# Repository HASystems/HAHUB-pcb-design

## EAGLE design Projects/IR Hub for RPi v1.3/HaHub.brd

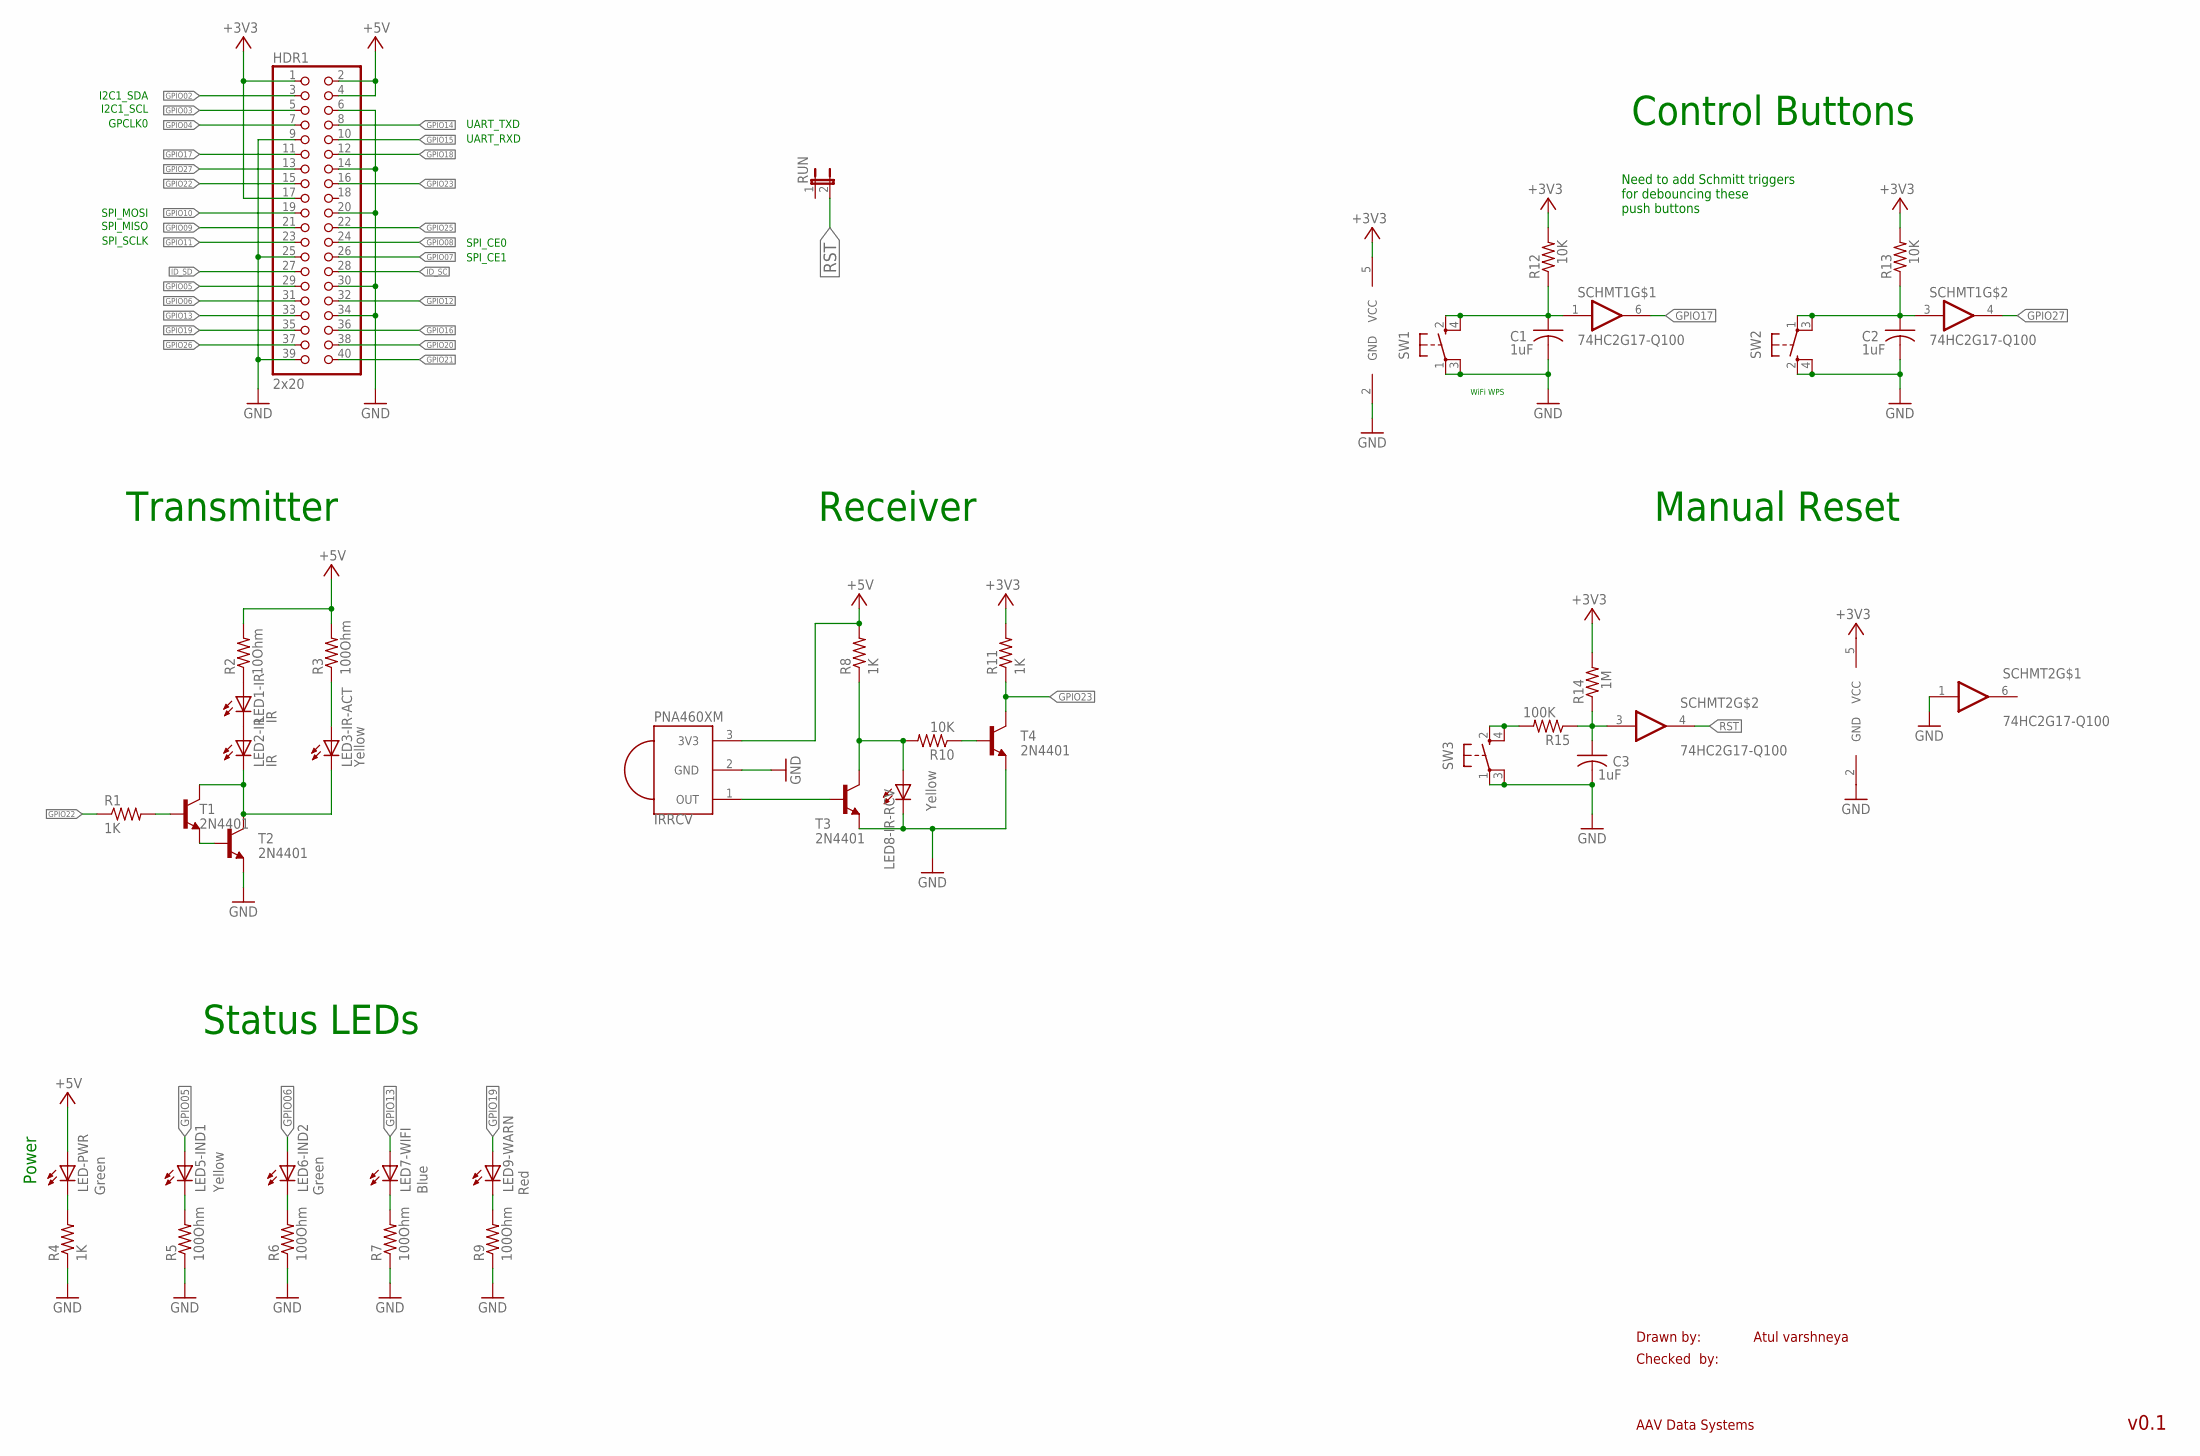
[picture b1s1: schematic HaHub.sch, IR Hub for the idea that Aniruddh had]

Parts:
C1, C2, C3: 1uF; C0805; MPN MC0805B104K160CT
HDR1: 2x20; 2X20
IRRCV: PNA460XM; MPN TSOP38238
LED1-IR, LED2-IR: IR; MICRO-SIDELED; MPN VSMB2943SLX01
LED3-IR-ACT, LED5-IND1, LED8-IR-RCV: Yellow; CHIPLED_0805; MPN 150080YS75000
LED6-IND2: Green; CHIPLED_0805; MPN 150080GS75000
LED7-WIFI: Blue; CHIPLED_0805; MPN 150080BS75000
LED9-WARN: Red; CHIPLED_0805; MPN 150080RS75000
LED-PWR: Green; CHIPLED_0805; MPN 150080GS75000
R1, R4, R8, R11: 1K; R0805; MPN CRCW08051K00FKEA
R2: 10Ohm; R0805; MPN CRCW080510R0FKEA
R3, R5, R6, R7, R9: 100Ohm; R0805; MPN CRCW0805100RFKEA
R10, R12, R13: 10K; R0805; MPN CRCW080510K0FKEA
R14: 1M; R0805; MPN CRCW08051M00FKEA
R15: 100K; R0805; MPN CRCW0805100KFKEA
RUN: RST; JP1; MPN 2211S-02G
SCHMT1, SCHMT2: 74HC2G17-Q100; SC-70-6L; MPN 74HC2G17GW,125
SW1, SW2, SW3: SPST_TACT-KMR2; KMR2
T1, T2, T3, T4: 2N4401; SOT23-BEC; MPN MMBT4401-TP

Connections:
+3V3: HDR1.1, HDR1.17, R11.2, R12.2, R13.2, R14.2, SCHMT1.5 (VCC), SCHMT2.5 (VCC)
+5V: HDR1.2, HDR1.4, IRRCV.3 (3V3), LED-PWR.A, R2.2, R3.2, R8.2
GND: C1.2, C2.2, C3.2, HDR1.6, HDR1.9, HDR1.14, HDR1.20, HDR1.25, HDR1.30, HDR1.34, HDR1.39, IRRCV.2 (GND), LED8-IR-RCV.C, R4.1, R5.1, R6.1, R7.1, R9.1, SCHMT1.2 (GND), SCHMT2.1 (I), SCHMT2.2 (GND), SW1.1, SW1.3 (P1), SW2.2 (S), SW2.4 (S1), SW3.1, SW3.3 (P1), T2.E, T3.E, T4.E
GPIO02: HDR1.3
GPIO03: HDR1.5
GPIO04: HDR1.7
GPIO05: HDR1.29, LED5-IND1.A
GPIO06: HDR1.31, LED6-IND2.A
GPIO07: HDR1.26
GPIO08: HDR1.24
GPIO09: HDR1.21
GPIO10: HDR1.19
GPIO11: HDR1.23
GPIO12: HDR1.32
GPIO13: HDR1.33, LED7-WIFI.A
GPIO14: HDR1.8
GPIO15: HDR1.10
GPIO16: HDR1.36
GPIO17: HDR1.11, SCHMT1.6 (O)
GPIO18: HDR1.12
GPIO19: HDR1.35, LED9-WARN.A
GPIO20: HDR1.38
GPIO21: HDR1.40
GPIO22: HDR1.15, R1.1
GPIO23: HDR1.16, R11.1, T4.C
GPIO25: HDR1.22
GPIO26: HDR1.37
GPIO27: HDR1.13, SCHMT1.4 (O)
ID_SC: HDR1.28
ID_SD: HDR1.27
unnamed: R15.2, SW3.2 (S), SW3.4 (S1)
unnamed: LED1-IR.A, R2.1
unnamed: LED1-IR.C, LED2-IR.A
unnamed: LED2-IR.C, LED3-IR-ACT.C, T1.C, T2.C
unnamed: R1.2, T1.B
unnamed: LED3-IR-ACT.A, R3.1
unnamed: LED5-IND1.C, R5.2
unnamed: IRRCV.1 (OUT), T3.B
unnamed: C1.1, R12.1, SCHMT1.1 (I), SW1.2 (S), SW1.4 (S1)
unnamed: LED8-IR-RCV.A, R8.1, R10.2, T3.C
unnamed: T1.E, T2.B
unnamed: C2.1, R13.1, SCHMT1.3 (I), SW2.1, SW2.3 (P1)
unnamed: C3.1, R14.1, R15.1, SCHMT2.3 (I)
unnamed: LED7-WIFI.C, R7.2
unnamed: LED9-WARN.C, R9.2
unnamed: LED6-IND2.C, R6.2
unnamed: LED-PWR.C, R4.2
unnamed: R10.1, T4.B
RST: RUN.2, SCHMT2.4 (O)

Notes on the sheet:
Drawn by:
Checked by:
AAV Data Systems
Atul varshneya
v0.1
Transmitter
Receiver
Status LEDs
Power
I2C1_SDA
I2C1_SCL
GPCLK0
SPI_MOSI
SPI_MISO
SPI_SCLK
SPI_CE0
SPI_CE1
UART_TXD
UART_RXD
Control Buttons
Manual Reset
WiFi WPS
Need to add Schmitt triggers for debouncing these push buttons

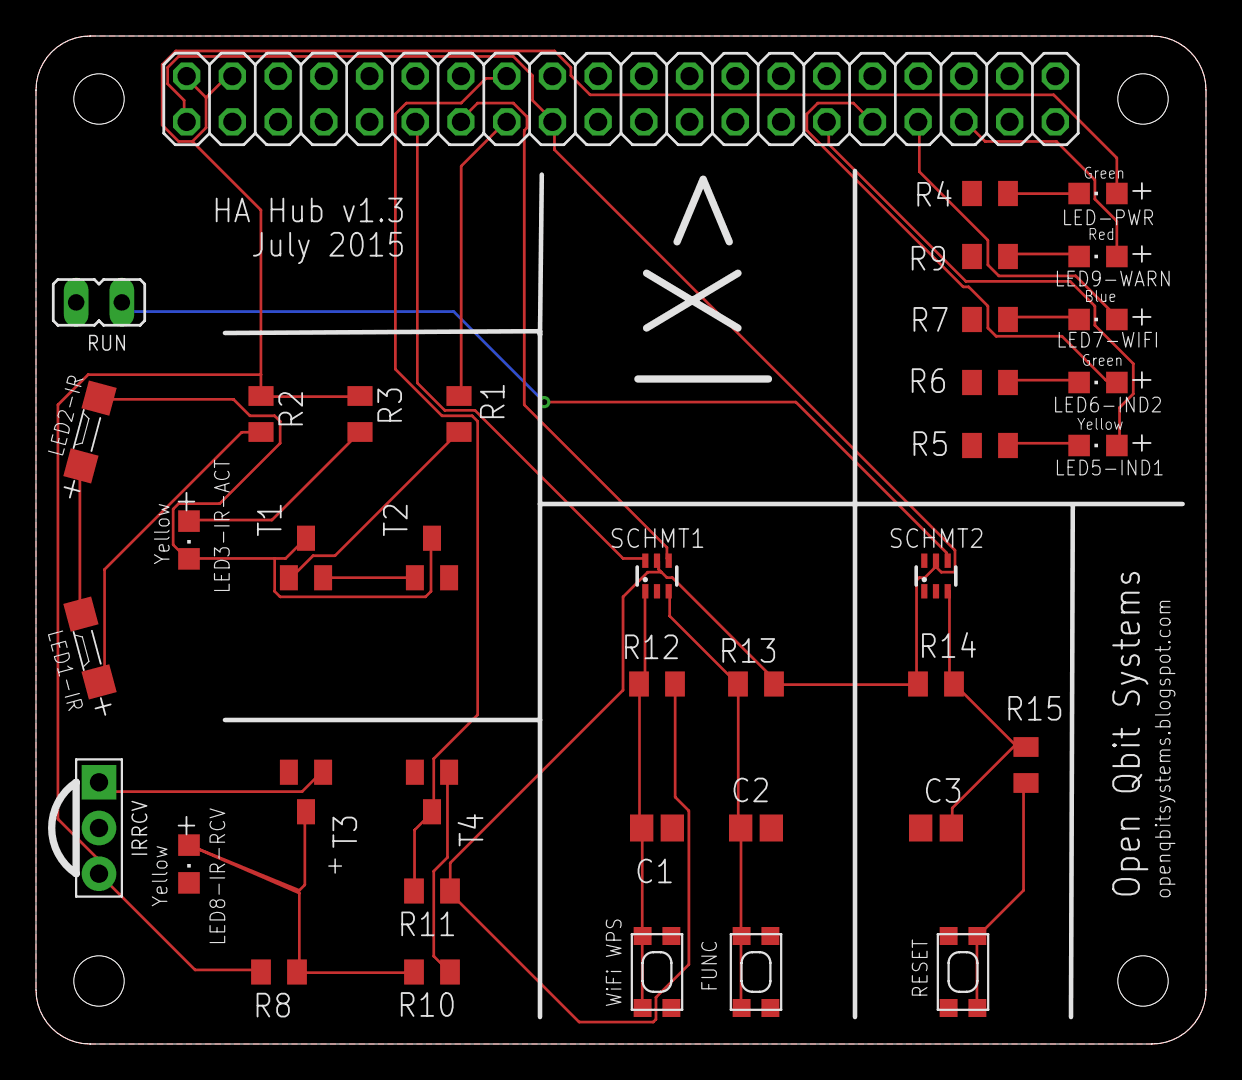
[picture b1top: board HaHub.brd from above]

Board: 2 copper layers, 65.0 x 56.0 mm, 39 parts (0 on the bottom side), 30 nets.

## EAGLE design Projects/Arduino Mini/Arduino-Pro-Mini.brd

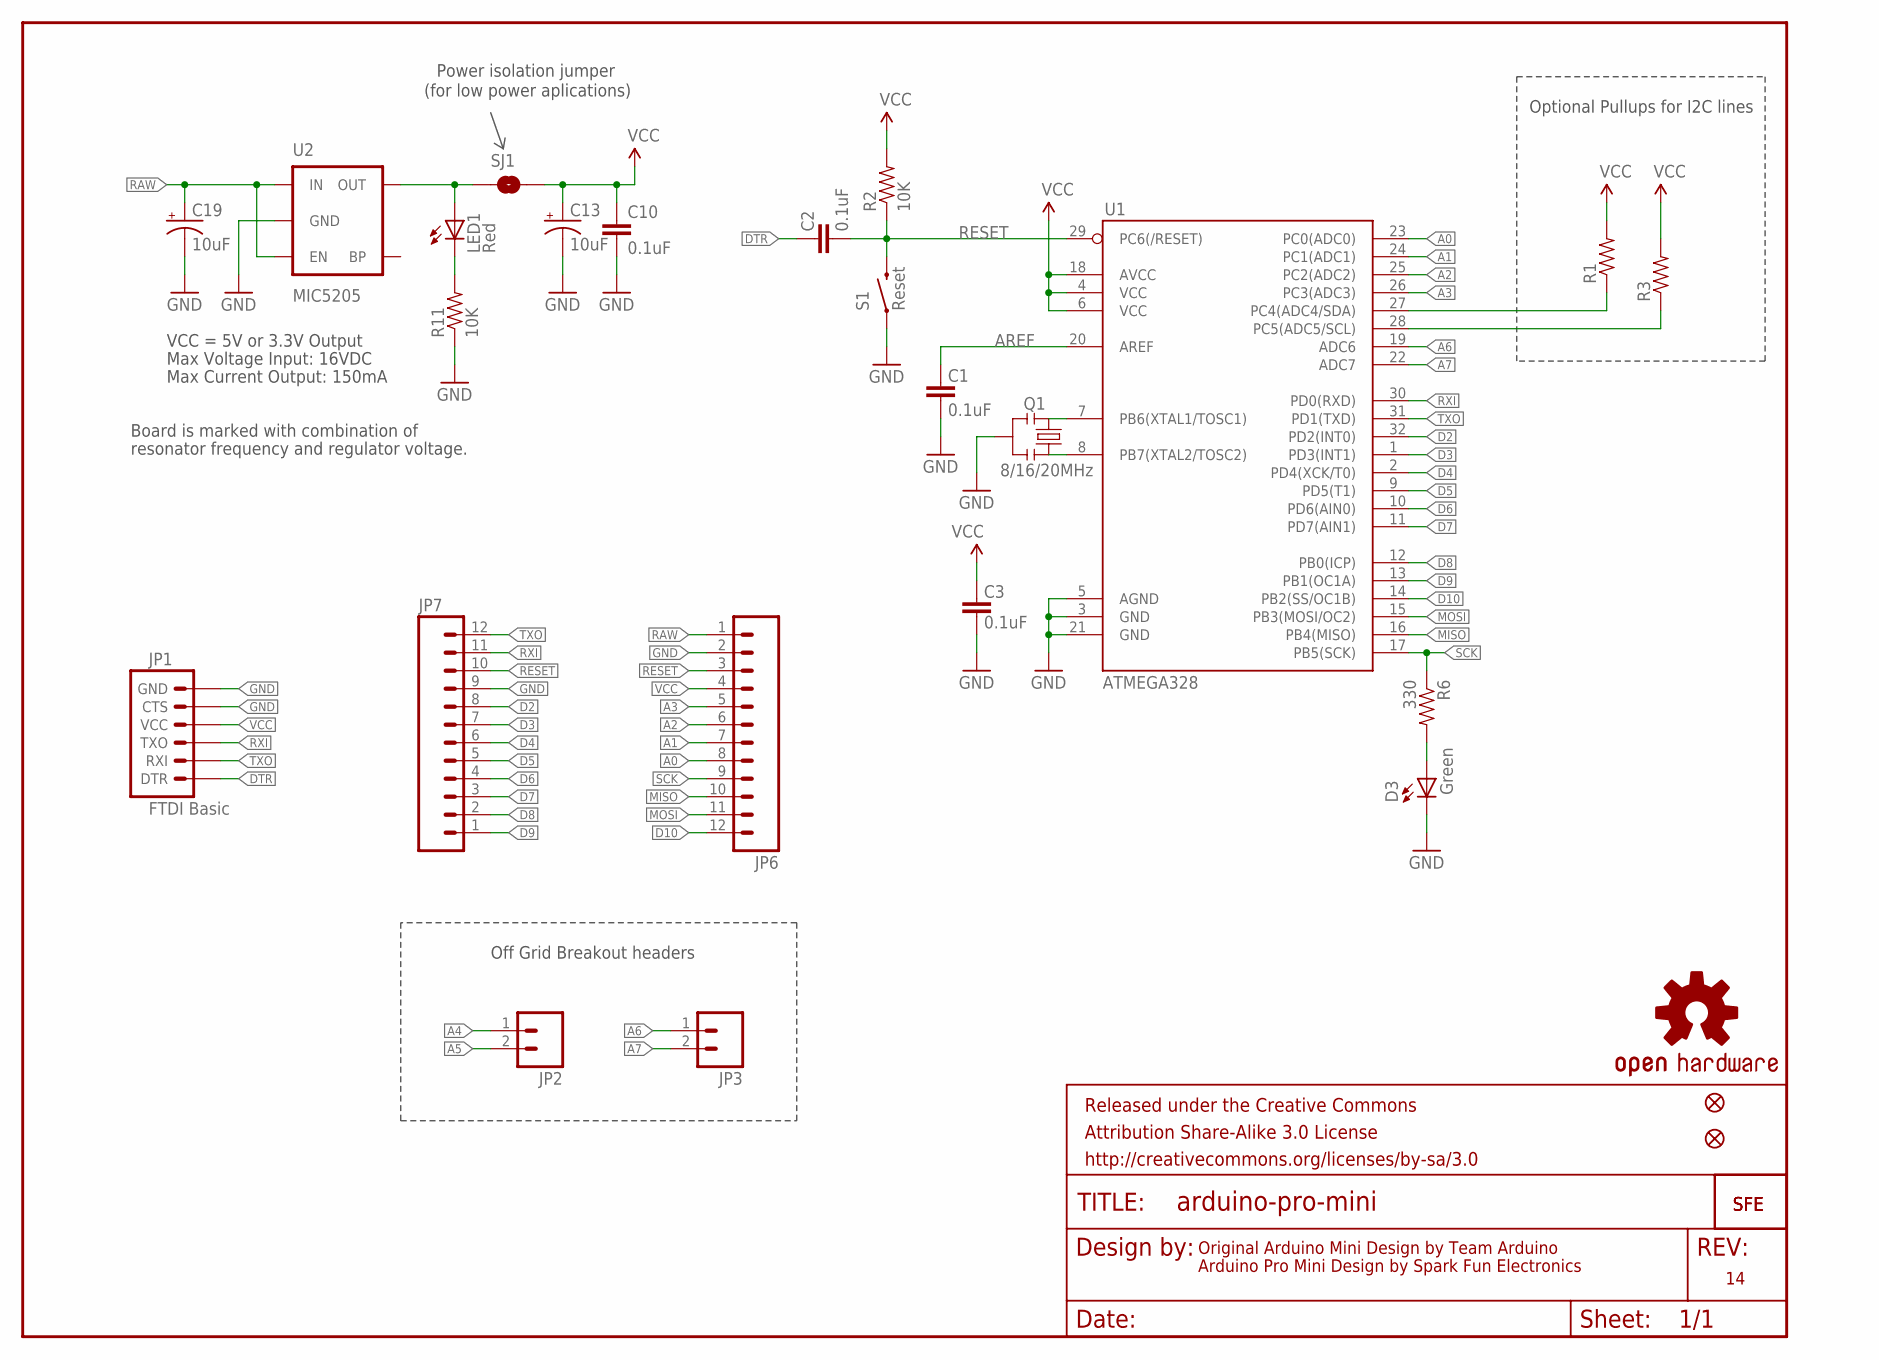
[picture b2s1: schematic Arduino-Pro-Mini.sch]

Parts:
C1, C2, C3, C10: 0.1uF; 0603-CAP
C13, C19: 10uF; EIA3216
D3: Green; 0603-LED-ALT1
FRAME1: FRAME-LETTER; CREATIVE_COMMONS
JP1: FTDI Basic; 1X06
JP2, JP3: M02PTH; 1X02
JP5, JP8: FIDUCIALUFIDUCIAL; MICRO-FIDUCIAL
JP6, JP7: M12PTH; 1X12
LED1: Red; 0603-LED-ALT1
Q1: 8/16/20MHz; RESONATOR-SMD-1:1
R1, R3: RESISTOR0603-RES; 0603-RES
R2, R11: 10K; 0603-RES
R6: 330; 0603-RES
S1: Reset; TACTILE-SWITCH-SMD-ALT01
SJ1: SOLDERJUMPERNC; SJ_2S
U1: ATMEGA328; TQFP32-08
U2: MIC5205; SOT23-5
U$1: LOGO-SFESK; SFE-LOGO-FLAME
U$3: OSHW-LOGOS; OSHW-LOGO-S
U$11: LOGO-SFENEW; SFE-NEW-WEBLOGO

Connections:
A0: JP6.8, U1.23 (PC0(ADC0))
A1: JP6.7, U1.24 (PC1(ADC1))
A2: JP6.6, U1.25 (PC2(ADC2))
A3: JP6.5, U1.26 (PC3(ADC3))
A4: JP2.1, R1.1, U1.27 (PC4(ADC4/SDA))
A5: JP2.2, R3.1, U1.28 (PC5(ADC5/SCL))
A6: JP3.1, U1.19 (ADC6)
A7: JP3.2, U1.22 (ADC7)
AREF: C1.2, U1.20 (AREF)
D2: JP7.8, U1.32 (PD2(INT0))
D3: JP7.7, U1.1 (PD3(INT1))
D4: JP7.6, U1.2 (PD4(XCK/T0))
D5: JP7.5, U1.9 (PD5(T1))
D6: JP7.4, U1.10 (PD6(AIN0))
D7: JP7.3, U1.11 (PD7(AIN1))
D8: JP7.2, U1.12 (PB0(ICP))
D9: JP7.1, U1.13 (PB1(OC1A))
D10: JP6.12, U1.14 (PB2(SS/OC1B))
DTR: C2.2, JP1.1 (DTR)
GND: C1.1, C3.1, C10.2, C13.C (-), C19.C (-), D3.C, JP1.5 (CTS), JP1.6 (GND), JP6.2, JP7.9, Q1.2, R11.1, S1.1, S1.2 (1), U1.3 (GND), U1.5 (AGND), U1.21 (GND), U2.2 (GND)
MISO: JP6.10, U1.16 (PB4(MISO))
MOSI: JP6.11, U1.15 (PB3(MOSI/OC2))
unnamed: Q1.3, U1.8 (PB7(XTAL2/TOSC2))
unnamed: Q1.1, U1.7 (PB6(XTAL1/TOSC1))
unnamed: LED1.A, SJ1.1, U2.5 (OUT)
unnamed: LED1.C, R11.2
unnamed: D3.A, R6.2
RAW: C19.A (+), JP6.1, U2.1 (IN), U2.3 (EN)
RESET: C2.1, JP6.3, JP7.10, R2.1, S1.3 (2), S1.4 (2), U1.29 (PC6(/RESET))
RXI: JP1.3 (TXO), JP7.11, U1.30 (PD0(RXD))
SCK: JP6.9, R6.1, U1.17 (PB5(SCK))
TXO: JP1.2 (RXI), JP7.12, U1.31 (PD1(TXD))
VCC: C3.2, C10.1, C13.A (+), JP1.4 (VCC), JP6.4, R1.2, R2.2, R3.2, SJ1.2, U1.4 (VCC), U1.6 (VCC), U1.18 (AVCC)

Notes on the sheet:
Original Arduino Mini Design by Team Arduino
Arduino Pro Mini Design by Spark Fun Electronics
Max Voltage Input: 16VDC
Max Current Output: 150mA
Board is marked with combination of
resonator frequency and regulator voltage.
VCC = 5V or 3.3V Output
Optional Pullups for I2C lines
Off Grid Breakout headers
Power isolation jumper
(for low power aplications)

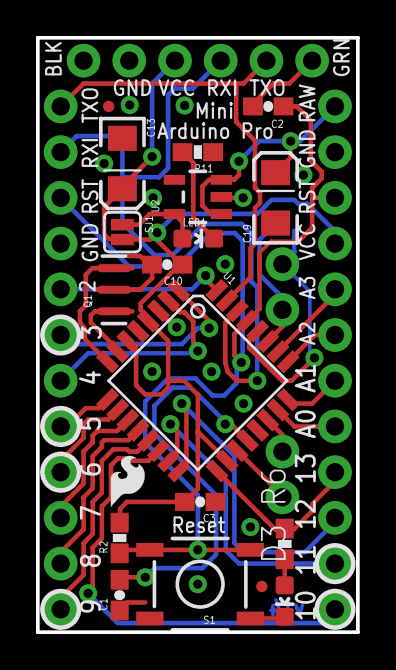
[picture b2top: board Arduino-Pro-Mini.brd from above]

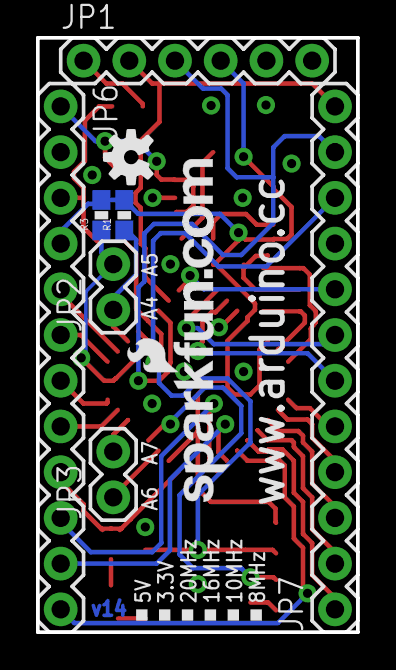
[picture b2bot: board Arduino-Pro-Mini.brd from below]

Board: 2 copper layers, 17.8 x 33.0 mm, 29 parts (9 on the bottom side), 33 nets.

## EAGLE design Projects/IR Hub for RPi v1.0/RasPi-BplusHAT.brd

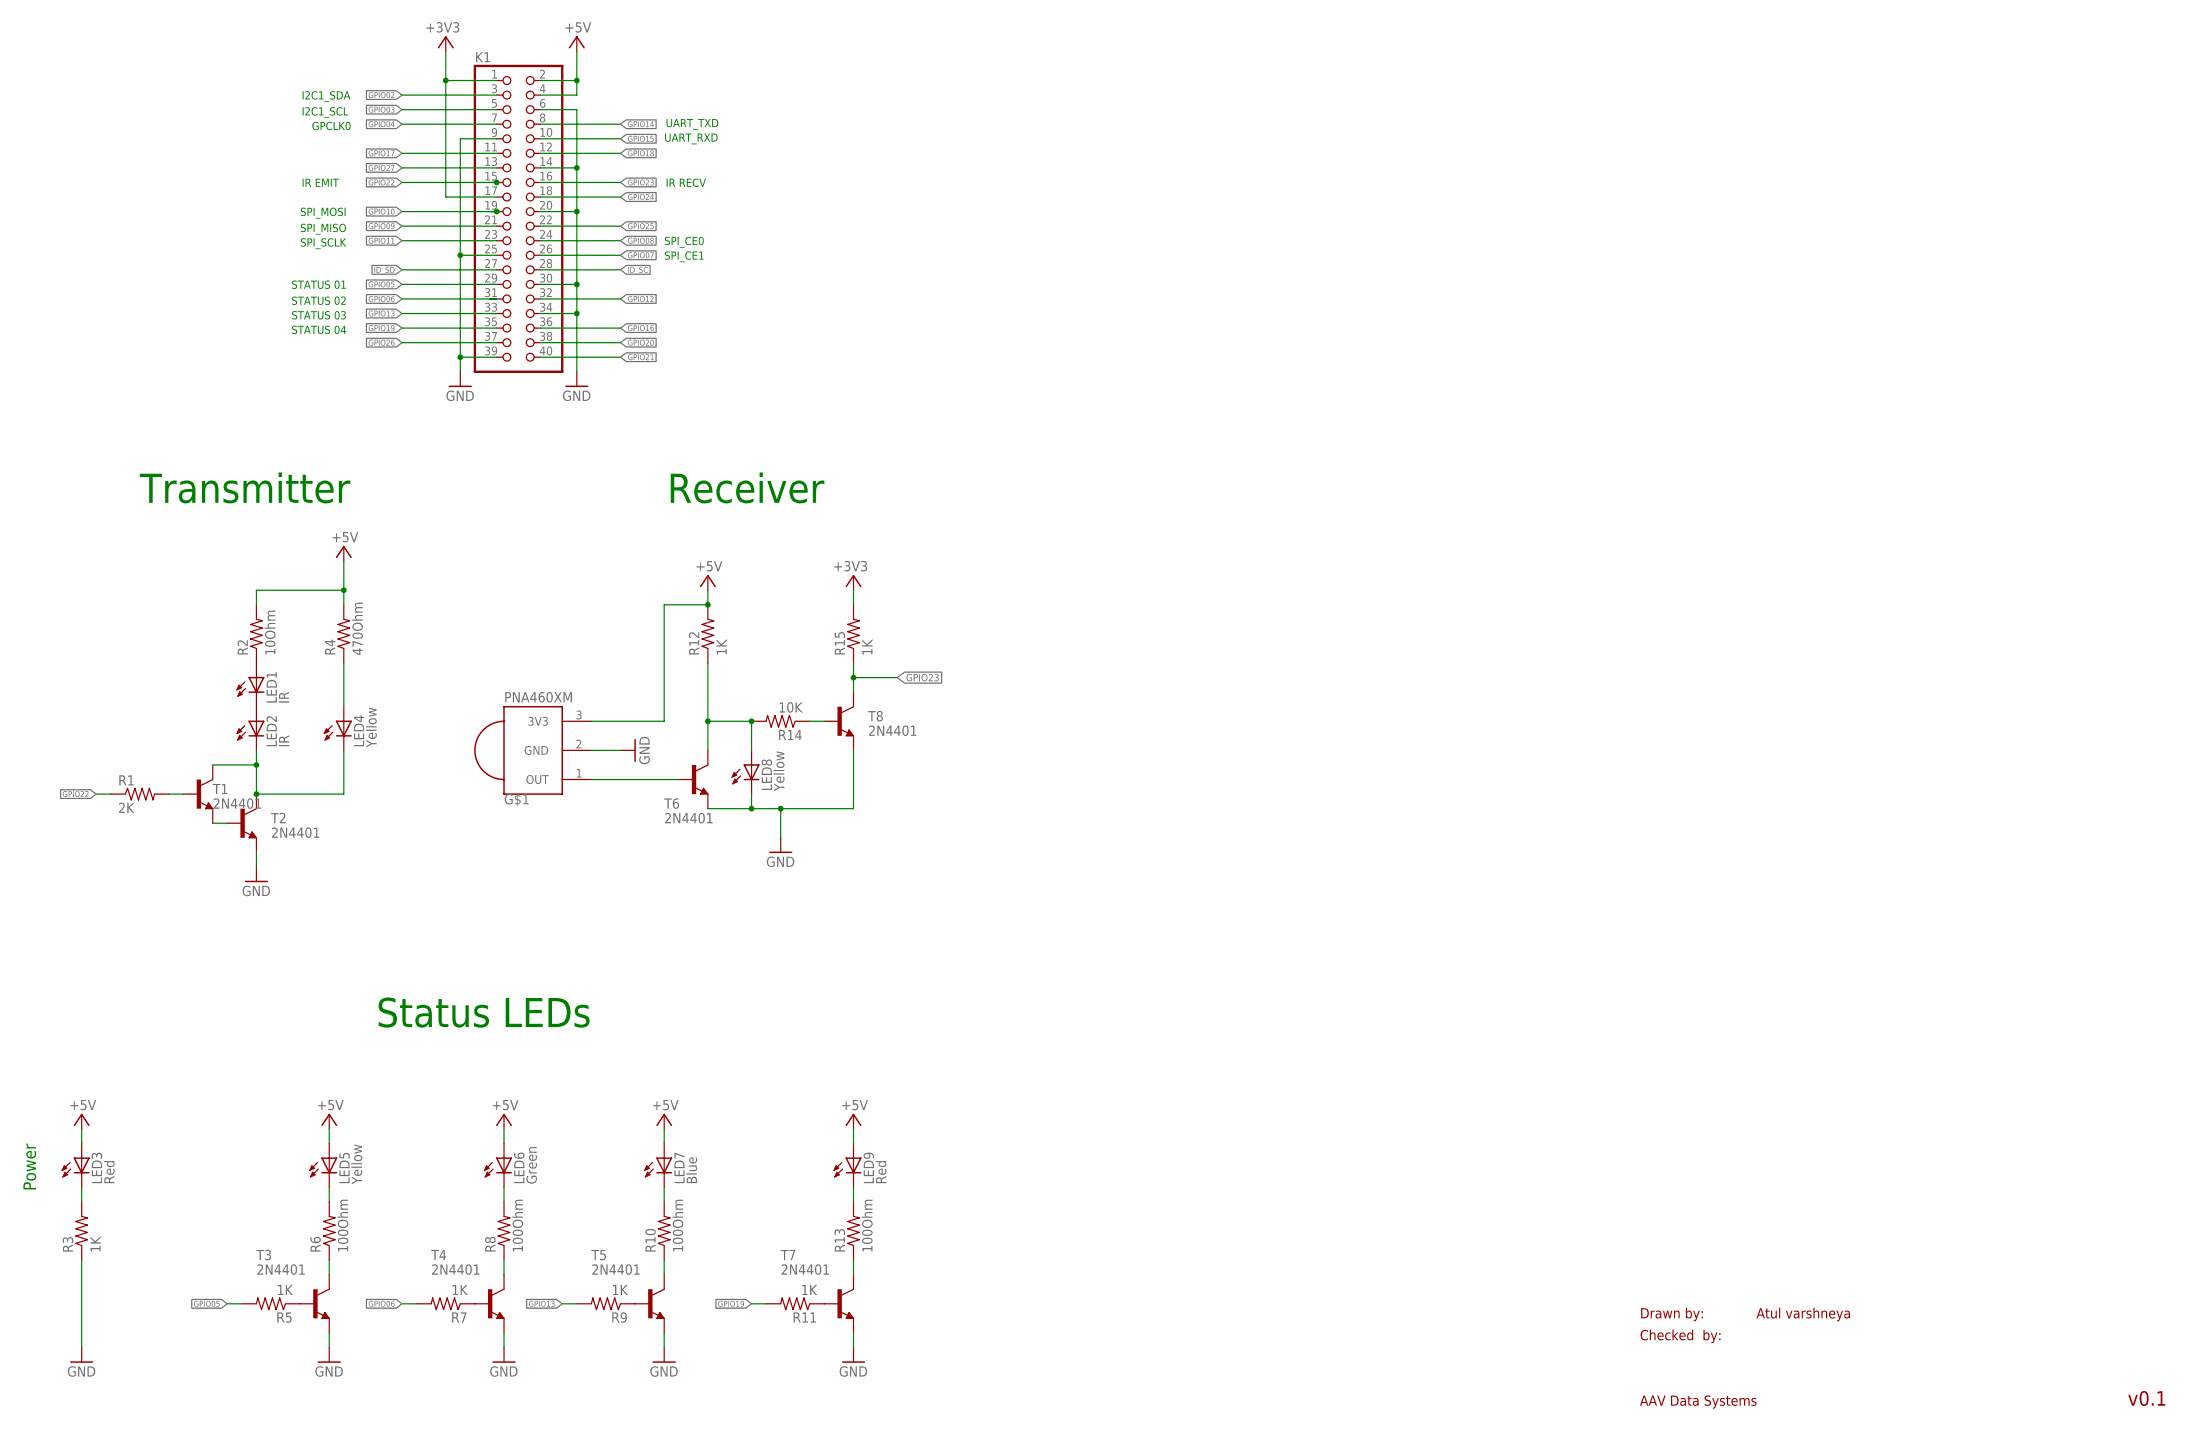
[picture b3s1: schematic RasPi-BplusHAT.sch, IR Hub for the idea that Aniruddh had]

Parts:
G$1: PNA460XM; MPN TSDP34138
K1: PINHD-2X20; 2X20
LED1, LED2: IR; MICRO-SIDELED; MPN VSMB10940X01
LED3, LED9: Red; CHIPLED_0805; MPN 150080RS75000
LED4, LED5, LED8: Yellow; CHIPLED_0805; MPN 150080YS75000
LED6: Green; CHIPLED_0805; MPN 150080GS75000
LED7: Blue; CHIPLED_0805; MPN 150080BS75000
R1: 2K; R0805; MPN CRCW08052K00JNEA
R2: 10Ohm; R0805; MPN RP2012S-100-F
R3, R5, R7, R9, R11, R12, R15: 1K; R0805; MPN CRCW08051K00JNEA
R4: 470Ohm; R0805; MPN CRCW0805470RJNEA
R6, R8, R10, R13: 100Ohm; R0805; MPN CRCW0805100RJNTA
R14: 10K; R0805; MPN CRCW080510K0JNEB
T1, T2, T3, T4, T5, T6, T7, T8: 2N4401; SOT23-BEC; MPN MMBT4401-TP

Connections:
+3V3: K1.1, K1.17, R15.2
+5V: G$1.3 (3V3), K1.2, K1.4, LED3.A, LED5.A, LED6.A, LED7.A, LED9.A, R2.2, R4.2, R12.2
GND: G$1.2 (GND), K1.6, K1.9, K1.14, K1.20, K1.25, K1.30, K1.34, K1.39, LED8.C, R3.1, T2.E, T3.E, T4.E, T5.E, T6.E, T7.E, T8.E
GPIO02: K1.3
GPIO03: K1.5
GPIO04: K1.7
GPIO05: K1.29, R5.2
GPIO06: K1.31, R7.2
GPIO07: K1.26
GPIO08: K1.24
GPIO09: K1.21
GPIO10: K1.19
GPIO11: K1.23
GPIO12: K1.32
GPIO13: K1.33, R9.2
GPIO14: K1.8
GPIO15: K1.10
GPIO16: K1.36
GPIO17: K1.11
GPIO18: K1.12
GPIO19: K1.35, R11.2
GPIO20: K1.38
GPIO21: K1.40
GPIO22: K1.15, R1.1
GPIO23: K1.16, R15.1, T8.C
GPIO24: K1.18
GPIO25: K1.22
GPIO26: K1.37
GPIO27: K1.13
ID_SC: K1.28
ID_SD: K1.27
unnamed: R6.1, T3.C
unnamed: LED1.A, R2.1
unnamed: LED1.C, LED2.A
unnamed: LED2.C, LED4.C, T1.C, T2.C
unnamed: R1.2, T1.B
unnamed: LED4.A, R4.1
unnamed: LED5.C, R6.2
unnamed: G$1.1 (OUT), T6.B
unnamed: R5.1, T3.B
unnamed: LED8.A, R12.1, R14.2, T6.C
unnamed: T1.E, T2.B
unnamed: R8.1, T4.C
unnamed: R10.1, T5.C
unnamed: LED9.C, R13.2
unnamed: R13.1, T7.C
unnamed: LED7.C, R10.2
unnamed: LED6.C, R8.2
unnamed: R7.1, T4.B
unnamed: R9.1, T5.B
unnamed: R11.1, T7.B
unnamed: LED3.C, R3.2
unnamed: R14.1, T8.B

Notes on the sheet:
Drawn by:
Checked by:
AAV Data Systems
Atul varshneya
v0.1
Transmitter
Receiver
Status LEDs
Power
IR RECV
IR EMIT
STATUS 01
STATUS 02
STATUS 03
STATUS 04
I2C1_SDA
I2C1_SCL
GPCLK0
SPI_MOSI
SPI_MISO
SPI_SCLK
SPI_CE0
SPI_CE1
UART_TXD
UART_RXD

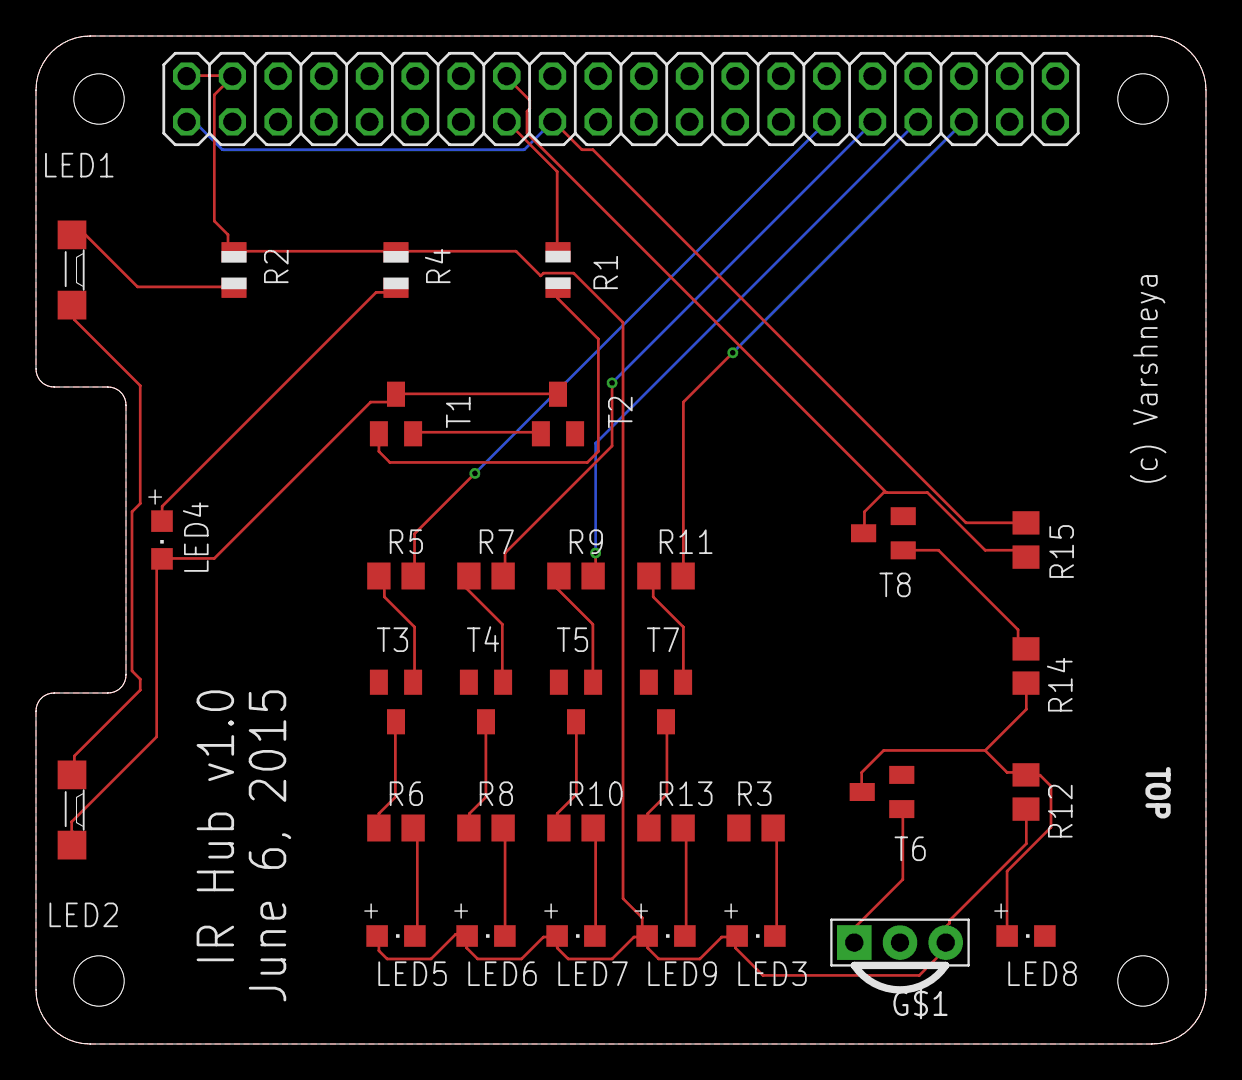
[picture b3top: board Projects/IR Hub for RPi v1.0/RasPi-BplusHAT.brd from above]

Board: 2 copper layers, 65.0 x 56.0 mm, 34 parts (0 on the bottom side), 31 nets.

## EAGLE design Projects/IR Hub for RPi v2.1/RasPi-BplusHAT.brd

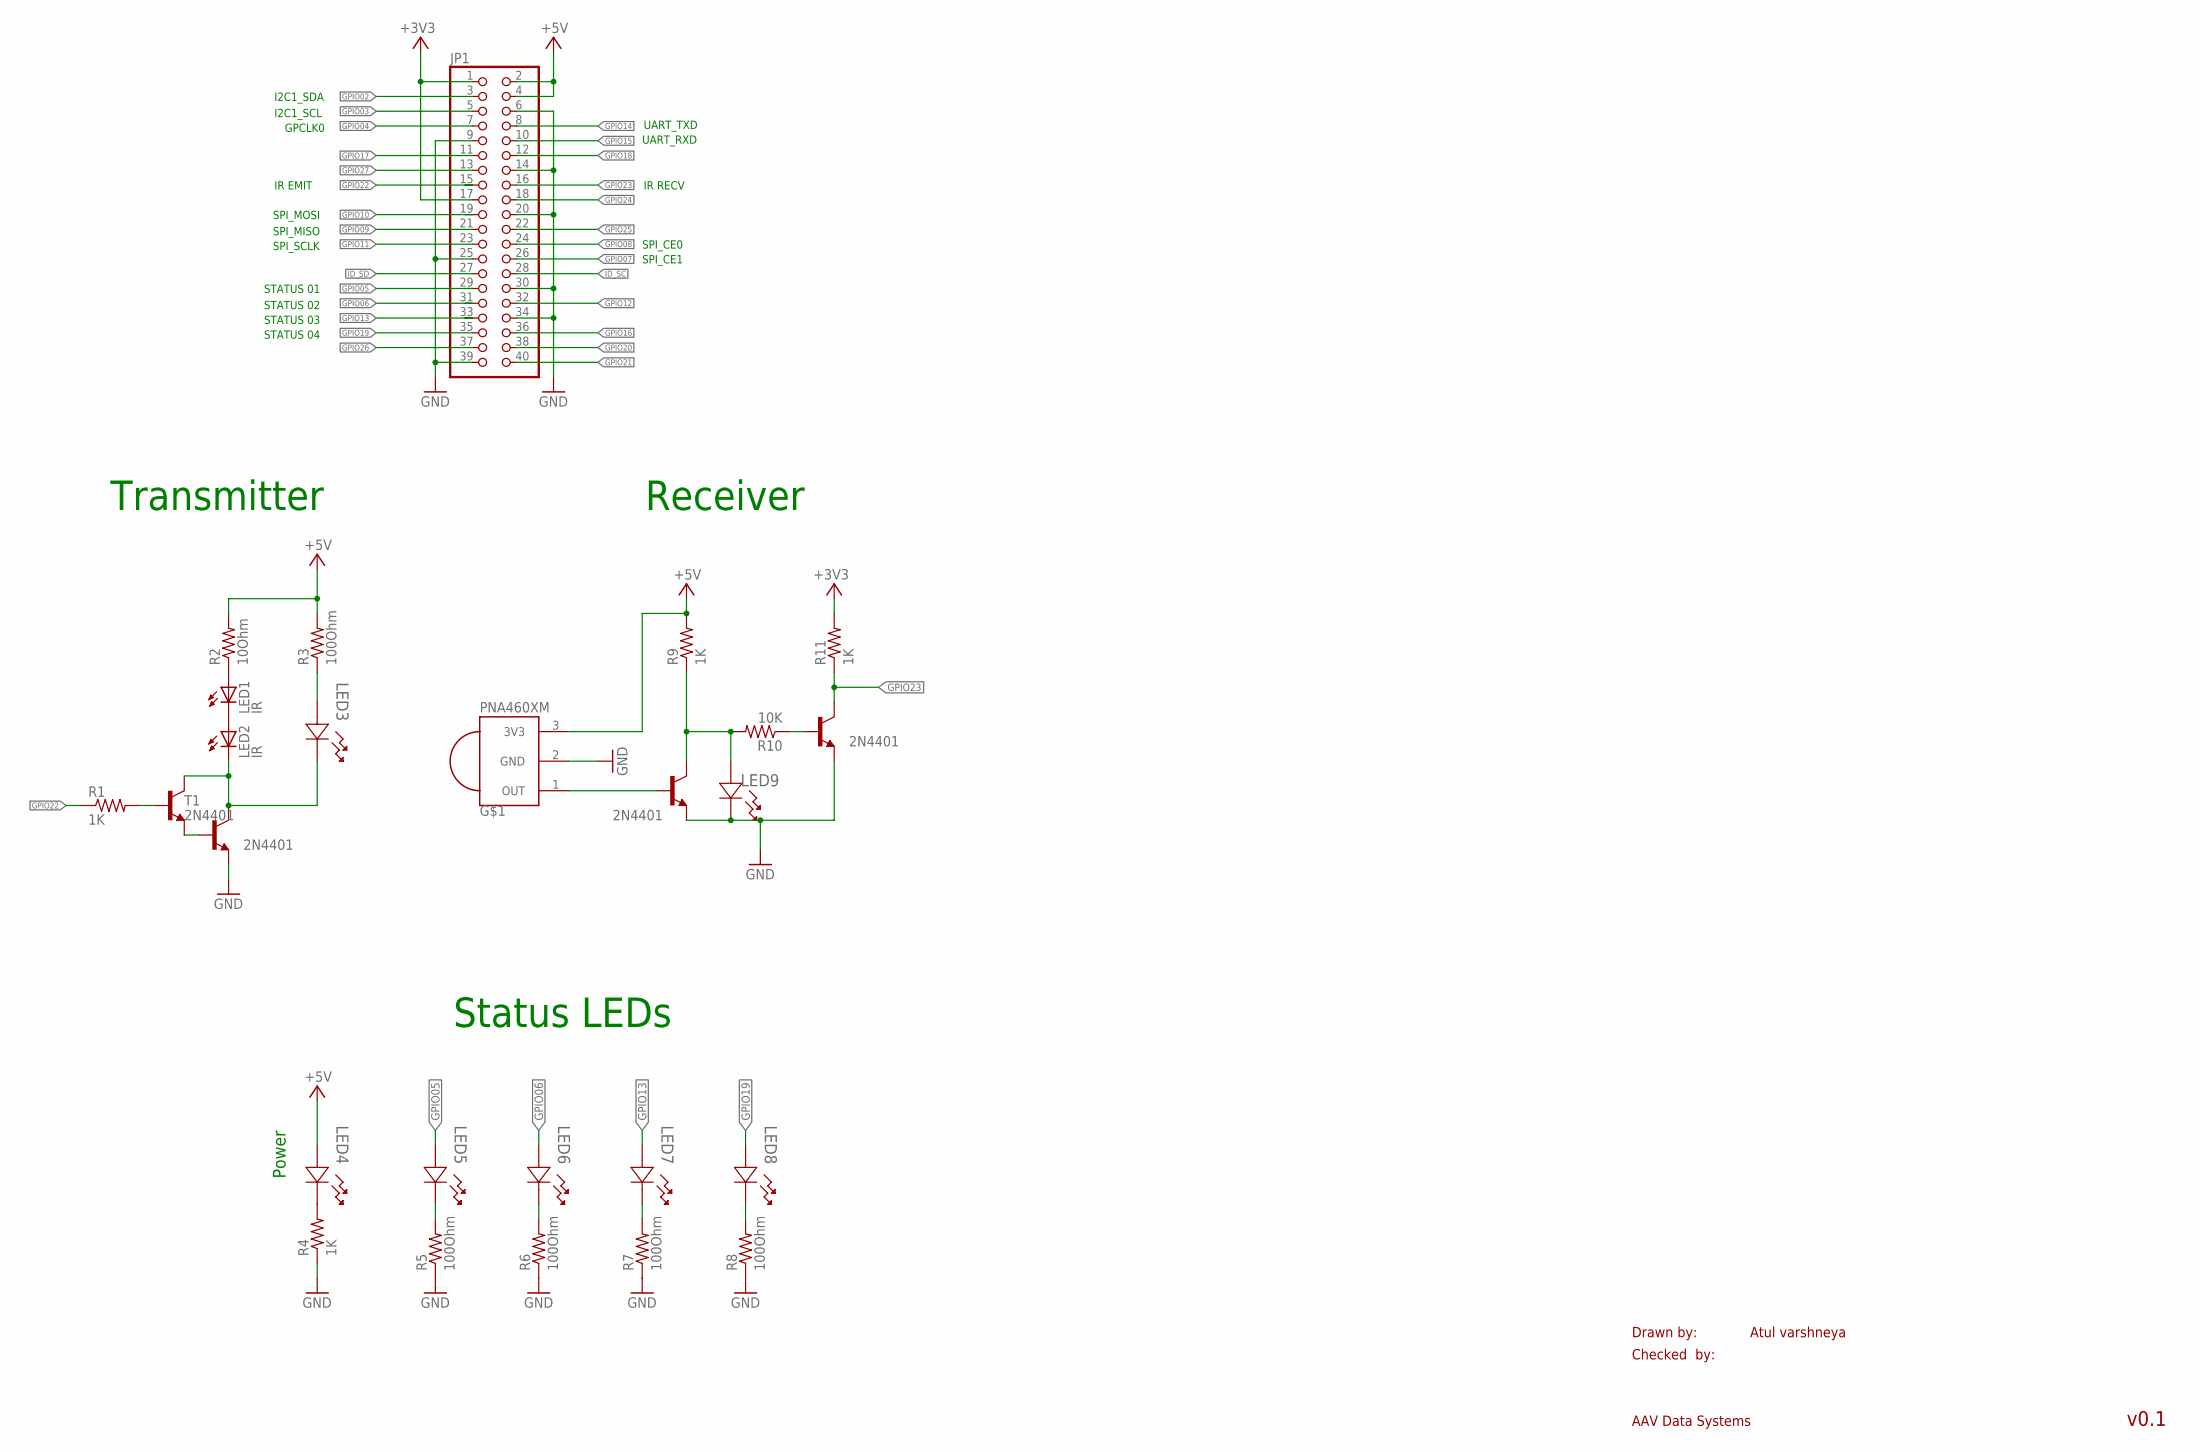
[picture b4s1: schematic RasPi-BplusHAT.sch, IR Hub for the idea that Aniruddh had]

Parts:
G$1: PNA460XM; MPN TSDP34138
JP1: PINHD-2X20; 2X20
LED1, LED2: IR; MICRO-SIDELED; MPN VSMB10940X01
LED3, LED6, LED8, LED9: 597-3401-407F; LED_597-3401-407F
LED4, LED5: 597-3311-407F; LED_597-3311-407F
LED7: 597-3111-407F; LED_597-3111-407F
R1, R4, R9, R11: 1K; R2010; MPN CRCW08051K00JNEA
R2: 10Ohm; R2010; MPN RP2012S-100-F
R3, R5, R6, R7, R8: 100Ohm; R2010; MPN CRCW0805100RJNTA
R10: 10K; R2010; MPN CRCW080510K0JNEB
T1, T2, T3, T4: 2N4401; SOT23-BEC; MPN MMBT4401-TP

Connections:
+3V3: JP1.1, JP1.17, R11.2
+5V: G$1.3 (3V3), JP1.2, JP1.4, LED4.2, R2.2, R3.2, R9.2
GND: G$1.2 (GND), JP1.6, JP1.9, JP1.14, JP1.20, JP1.25, JP1.30, JP1.34, JP1.39, LED9.1, R4.1, R5.1, R6.1, R7.1, R8.1, T2.E, T3.E, T4.E
GPIO02: JP1.3
GPIO03: JP1.5
GPIO04: JP1.7
GPIO05: JP1.29, LED5.2
GPIO06: JP1.31, LED6.2
GPIO07: JP1.26
GPIO08: JP1.24
GPIO09: JP1.21
GPIO10: JP1.19
GPIO11: JP1.23
GPIO12: JP1.32
GPIO13: JP1.33, LED7.2
GPIO14: JP1.8
GPIO15: JP1.10
GPIO16: JP1.36
GPIO17: JP1.11
GPIO18: JP1.12
GPIO19: JP1.35, LED8.2
GPIO20: JP1.38
GPIO21: JP1.40
GPIO22: JP1.15, R1.1
GPIO23: JP1.16, R11.1, T4.C
GPIO24: JP1.18
GPIO25: JP1.22
GPIO26: JP1.37
GPIO27: JP1.13
ID_SC: JP1.28
ID_SD: JP1.27
unnamed: LED1.A, R2.1
unnamed: LED1.C, LED2.A
unnamed: LED2.C, LED3.1, T1.C, T2.C
unnamed: R1.2, T1.B
unnamed: LED3.2, R3.1
unnamed: LED5.1, R5.2
unnamed: G$1.1 (OUT), T3.B
unnamed: LED9.2, R9.1, R10.2, T3.C
unnamed: T1.E, T2.B
unnamed: LED8.1, R8.2
unnamed: LED7.1, R7.2
unnamed: LED6.1, R6.2
unnamed: LED4.1, R4.2
unnamed: R10.1, T4.B

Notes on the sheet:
Drawn by:
Checked by:
AAV Data Systems
Atul varshneya
v0.1
Transmitter
Receiver
Status LEDs
Power
IR RECV
IR EMIT
STATUS 01
STATUS 02
STATUS 03
STATUS 04
I2C1_SDA
I2C1_SCL
GPCLK0
SPI_MOSI
SPI_MISO
SPI_SCLK
SPI_CE0
SPI_CE1
UART_TXD
UART_RXD

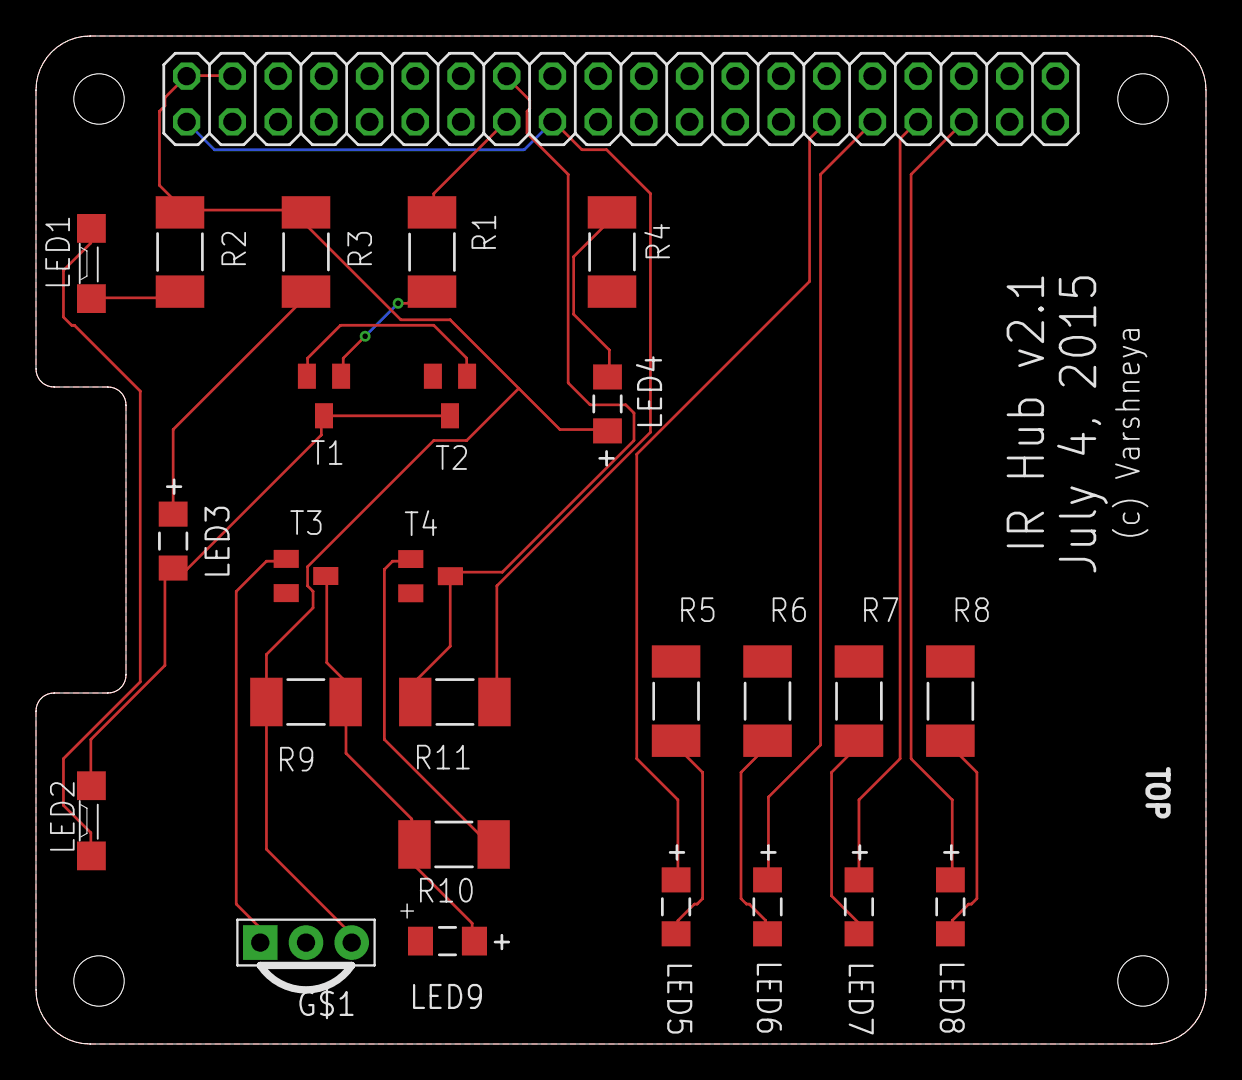
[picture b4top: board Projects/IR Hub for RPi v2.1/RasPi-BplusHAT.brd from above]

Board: 2 copper layers, 65.0 x 56.0 mm, 26 parts (0 on the bottom side), 23 nets.

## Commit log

2015-07-18 :boom::camel: Added .gitattributes & .gitignore files
2015-07-18 all pcbv design files July 17
2015-07-18 OSHPark Gerber files
2015-07-18 Removing unnecessary backup files
2015-07-19 removed Watchdog
    ... as there is a hardware watchdog on Raspberry Pi, and a good
    watchdog daemon framework for health monitoring
2015-07-20 Cleaned up the board layout
    ... with name and blog URL added; added a smoothening aspect in the
    circuit for the RESET push button.
2015-07-24 relocated IRRCV
2015-07-24 Revert "relocated IRRCV"
    This reverts commit a5258da49ac38eba7fe15d274991cfdce8bd6922.
2015-07-24 removed 2.1, 3.0 as they have been renamed
2015-07-24 Revert "removed 2.1, 3.0 as they have been renamed"
    This reverts commit 907848cc4251bd9049c3255ebf64068e5c6669ba.
2015-07-24 Revert "Revert "removed 2.1, 3.0 as they have been renamed""
    This reverts commit 996d22f48f320dafb8909d2bebf4a592d2e58273.
2015-07-24 Revert "Revert "relocated IRRCV""
    This reverts commit e9af4263ddd1cfc11cb1365f6dffa75911e4cf46.
2015-07-24 Relocated IR-RCV
2015-07-24 Deleted unnecessary project folders
2015-07-24 minor teaks to silk, changed one LED to blue color
2015-07-24 near final version - checkpoint
    Pending AIs -
    check polarity of the IR LEDs
    check the buffer circuit on breadboard
2015-07-25 fixed the visible layers in sch file
2015-07-25 Nothing significant, just the epf file updated due to some viewing of the files
2015-07-27 Tilted the IR LEDs
    Tilted the IR LEDs 10 degrees each (and moved IRRCV accordingly) to
    increase the total coverage angle
2015-08-01 Board layout changed
    Removed the cutout in the board thus moved the IR emitters a bit
    forward, avoiding the obstruction from the IRRCV when angled at 15deg.
2015-08-03 Changed v1.3 board 'via' drill size to 13mil. Plus some house keeping,
2015-08-12 HaHub v1.3 completed, Moved on to v1.4.
2015-08-17 Copied the v1.3 into v1.4 folder, and noted down v1.3 LED and buttons locations
2016-02-16 edited some text in the schematic to make it more clear
2016-08-08 Added teh PCB pictures

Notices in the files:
parts and their libraries:
SparkFun-Aesthetics: Licensing: CC v3.0 Share-Alike You are welcome to use this library for commercial purposes.
SparkFun-Aesthetics: Released under the Creative Commons Attribution Share-Alike 3.0 License
SparkFun-Aesthetics: http://creativecommons.org/licenses/by-sa/3.0
